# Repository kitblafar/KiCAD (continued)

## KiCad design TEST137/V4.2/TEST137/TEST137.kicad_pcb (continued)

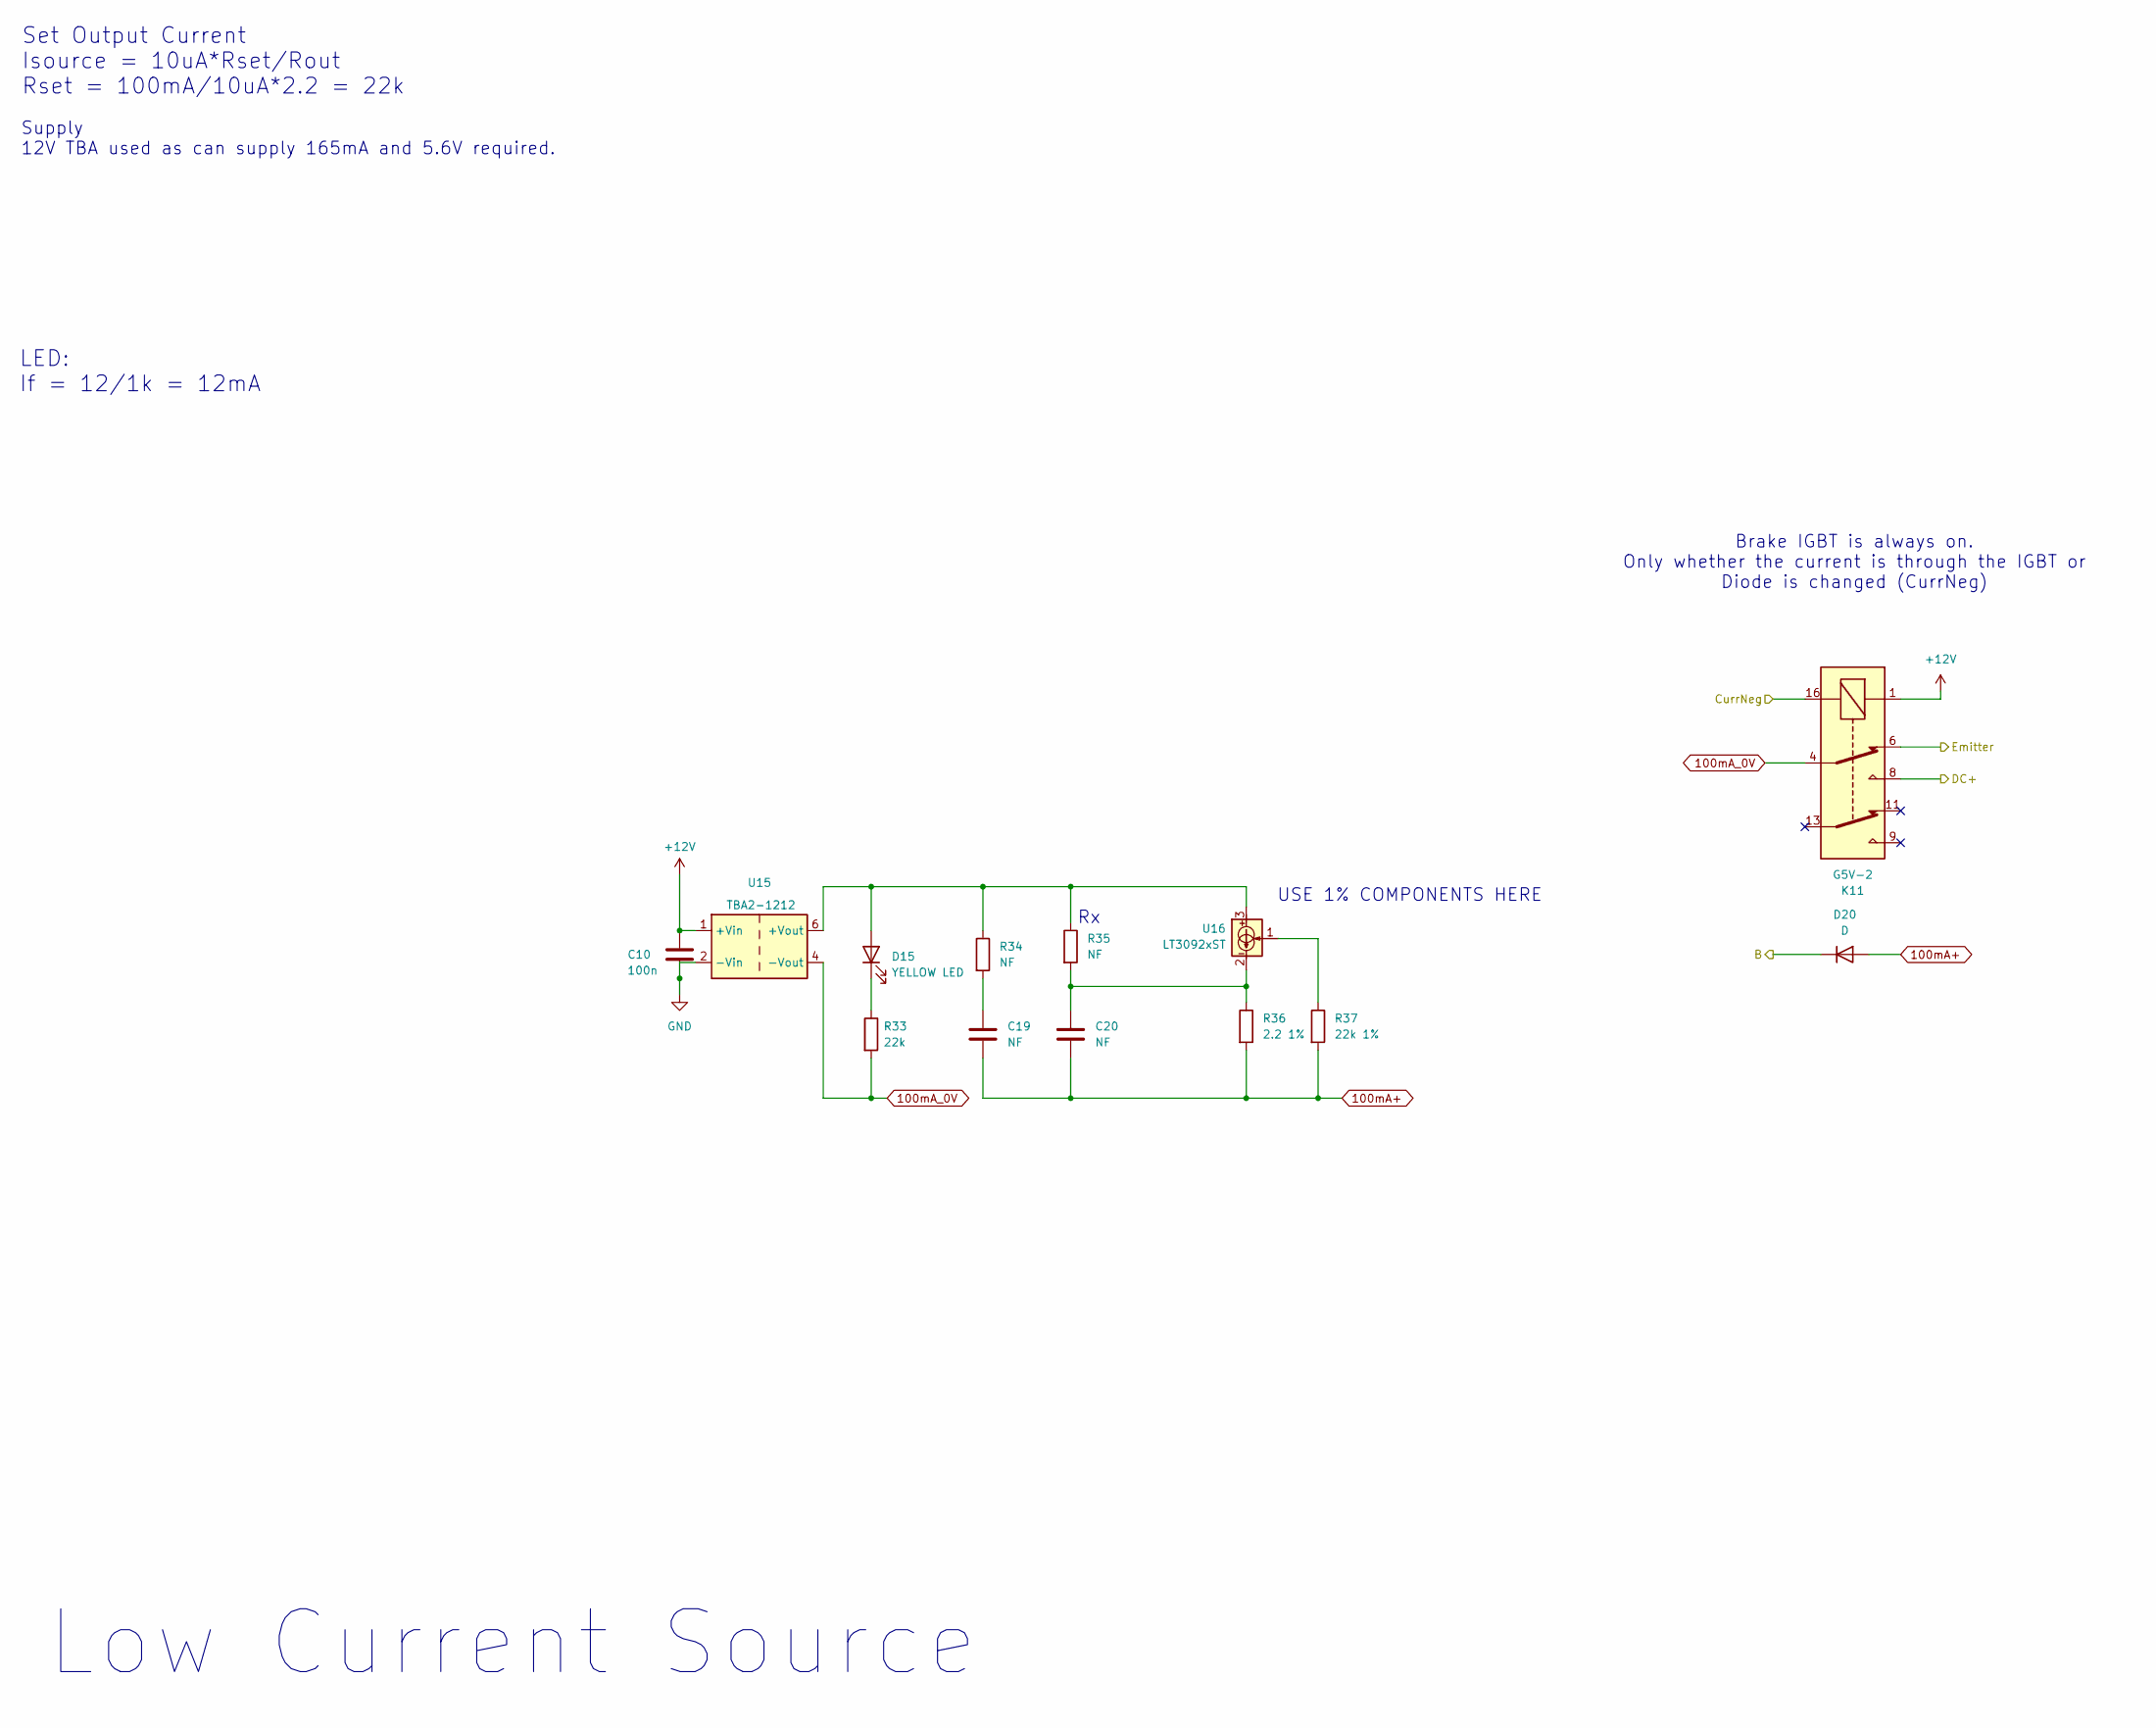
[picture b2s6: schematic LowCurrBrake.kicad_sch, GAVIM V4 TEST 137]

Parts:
C10: 100n; C_0603_1608Metric_Pad1.08x0.95mm_HandSolder
C19, C20: NF; C_0603_1608Metric_Pad1.08x0.95mm_HandSolder
D15: YELLOW LED; LED_D4.0mm
D20: D; BAS16
K11: G5V-2; Relay_DPDT_Omron_G5V-2
R33: 22k; R_0603_1608Metric_Pad0.98x0.95mm_HandSolder
R34, R35: NF; R_0603_1608Metric_Pad0.98x0.95mm_HandSolder
R36: 2.2 1%; R_0603_1608Metric_Pad0.98x0.95mm_HandSolder
R37: 22k 1%; R_0603_1608Metric_Pad0.98x0.95mm_HandSolder
U15: TBA2-1212; TBA21213
U16: LT3092xST; SOT-223-3_TabPin2

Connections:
100mA+: C19.2, C20.2, D20.2 (A), R36.2, R37.2
100mA_0V: K11.4, R33.2, U15.4 (-Vout)
+12V: C10.1, K11.1, U15.1 (+Vin); also elsewhere on the board
/Low Current/CurrNeg12V: K11.16; also elsewhere on the board
B: D20.1 (K); also elsewhere on the board
Bem: K11.6; also elsewhere on the board
DC+: K11.8; also elsewhere on the board
GND: C10.2, U15.2 (-Vin); also elsewhere on the board
unnamed: C19.1, R34.2
unnamed: C20.1, R35.2, R36.1, U16.2
unnamed: D15.2 (A), R34.1, R35.1, U15.6 (+Vout), U16.3
unnamed: D15.1 (K), R33.1
unnamed: R37.1, U16.1

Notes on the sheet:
Supply 12V TBA used as can supply 165mA and 5.6V required.
Brake IGBT is always on. Only whether the current is through the IGBT or Diode is changed (CurrNeg)
LED: If = 12/1k = 12mA
Set Output Current Isource = 10uA*Rset/Rout Rset = 100mA/10uA*2.2 = 22k
USE 1% COMPONENTS HERE
Low Current Source

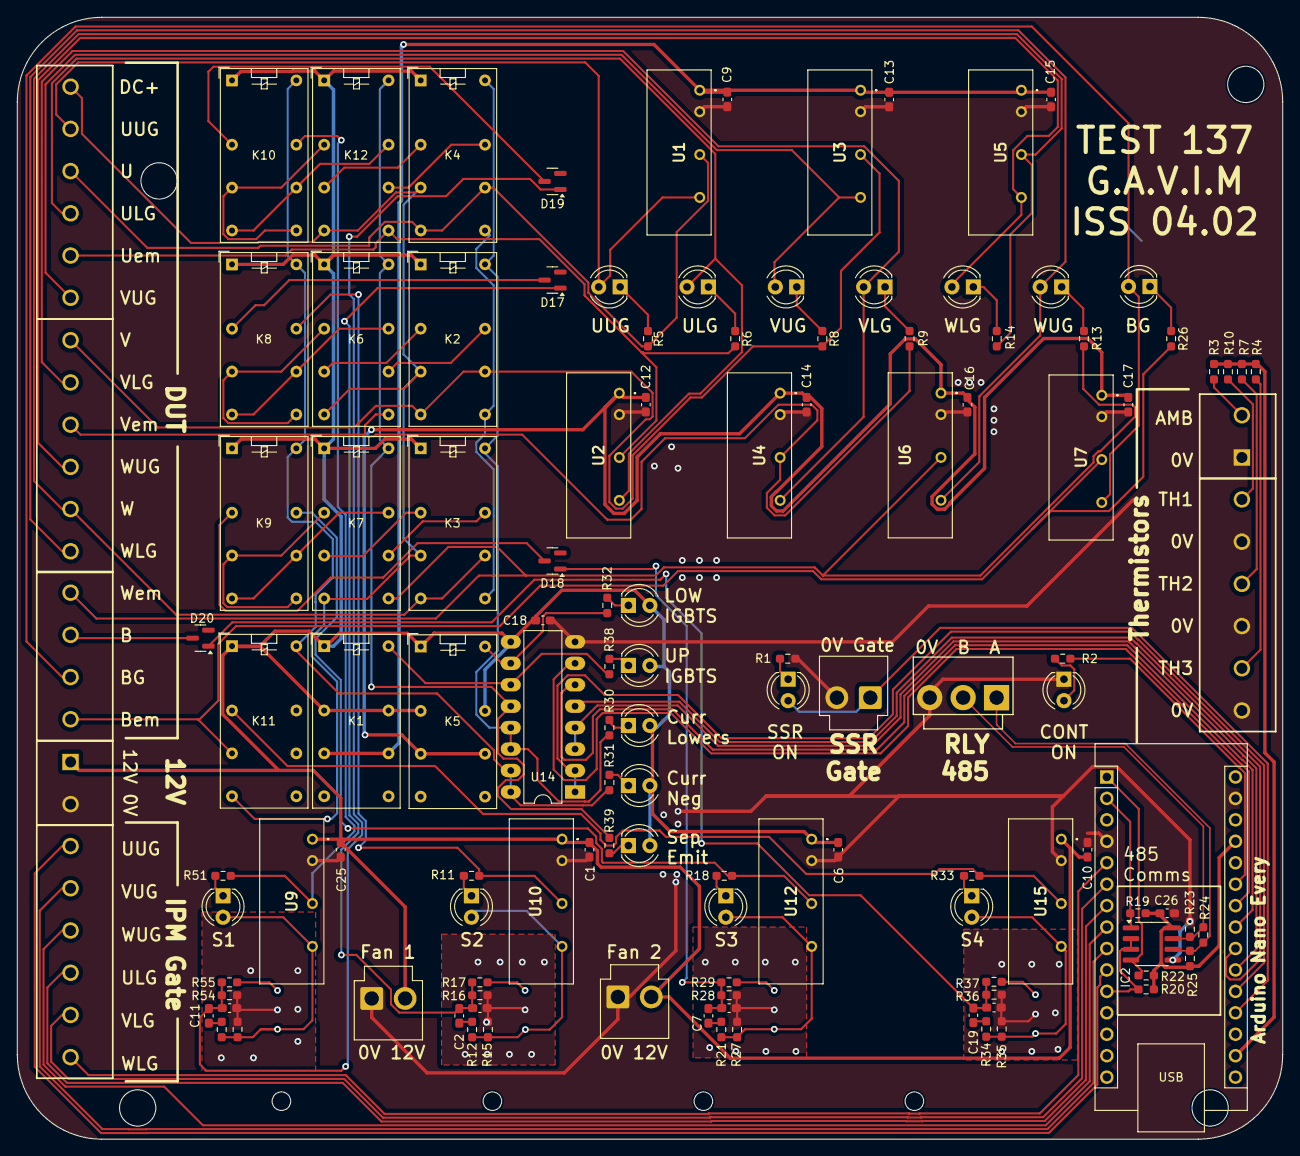
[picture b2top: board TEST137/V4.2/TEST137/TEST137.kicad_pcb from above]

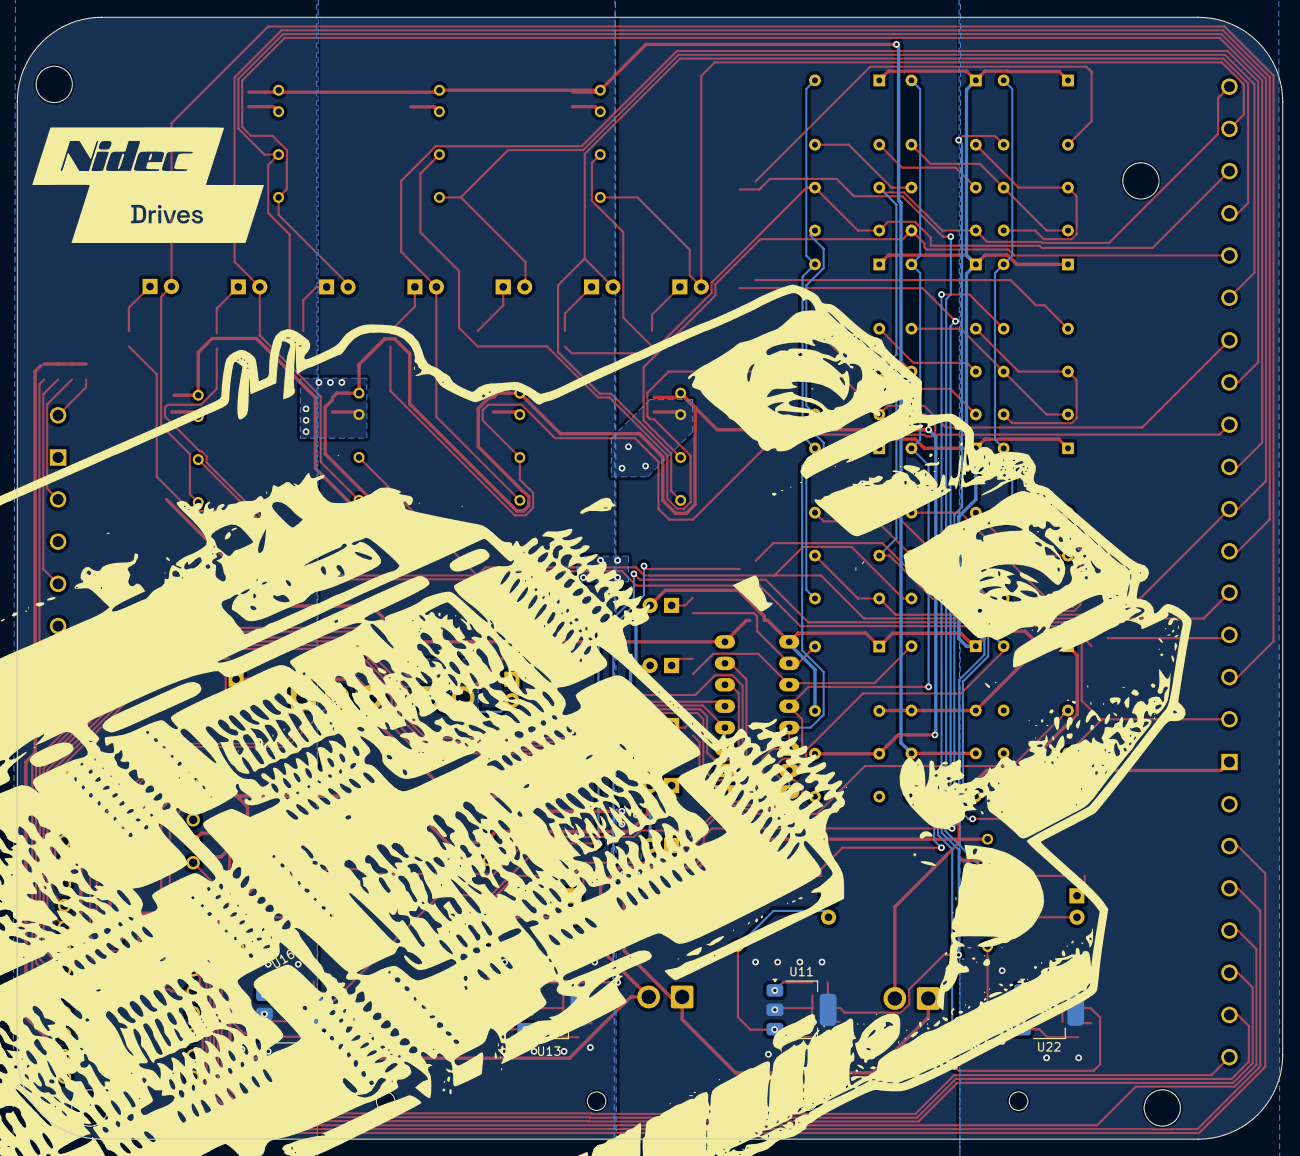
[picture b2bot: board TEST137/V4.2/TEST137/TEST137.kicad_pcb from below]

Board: 2 copper layers, 149.9 x 132.9 mm, 128 parts (4 on the bottom side), 107 nets.

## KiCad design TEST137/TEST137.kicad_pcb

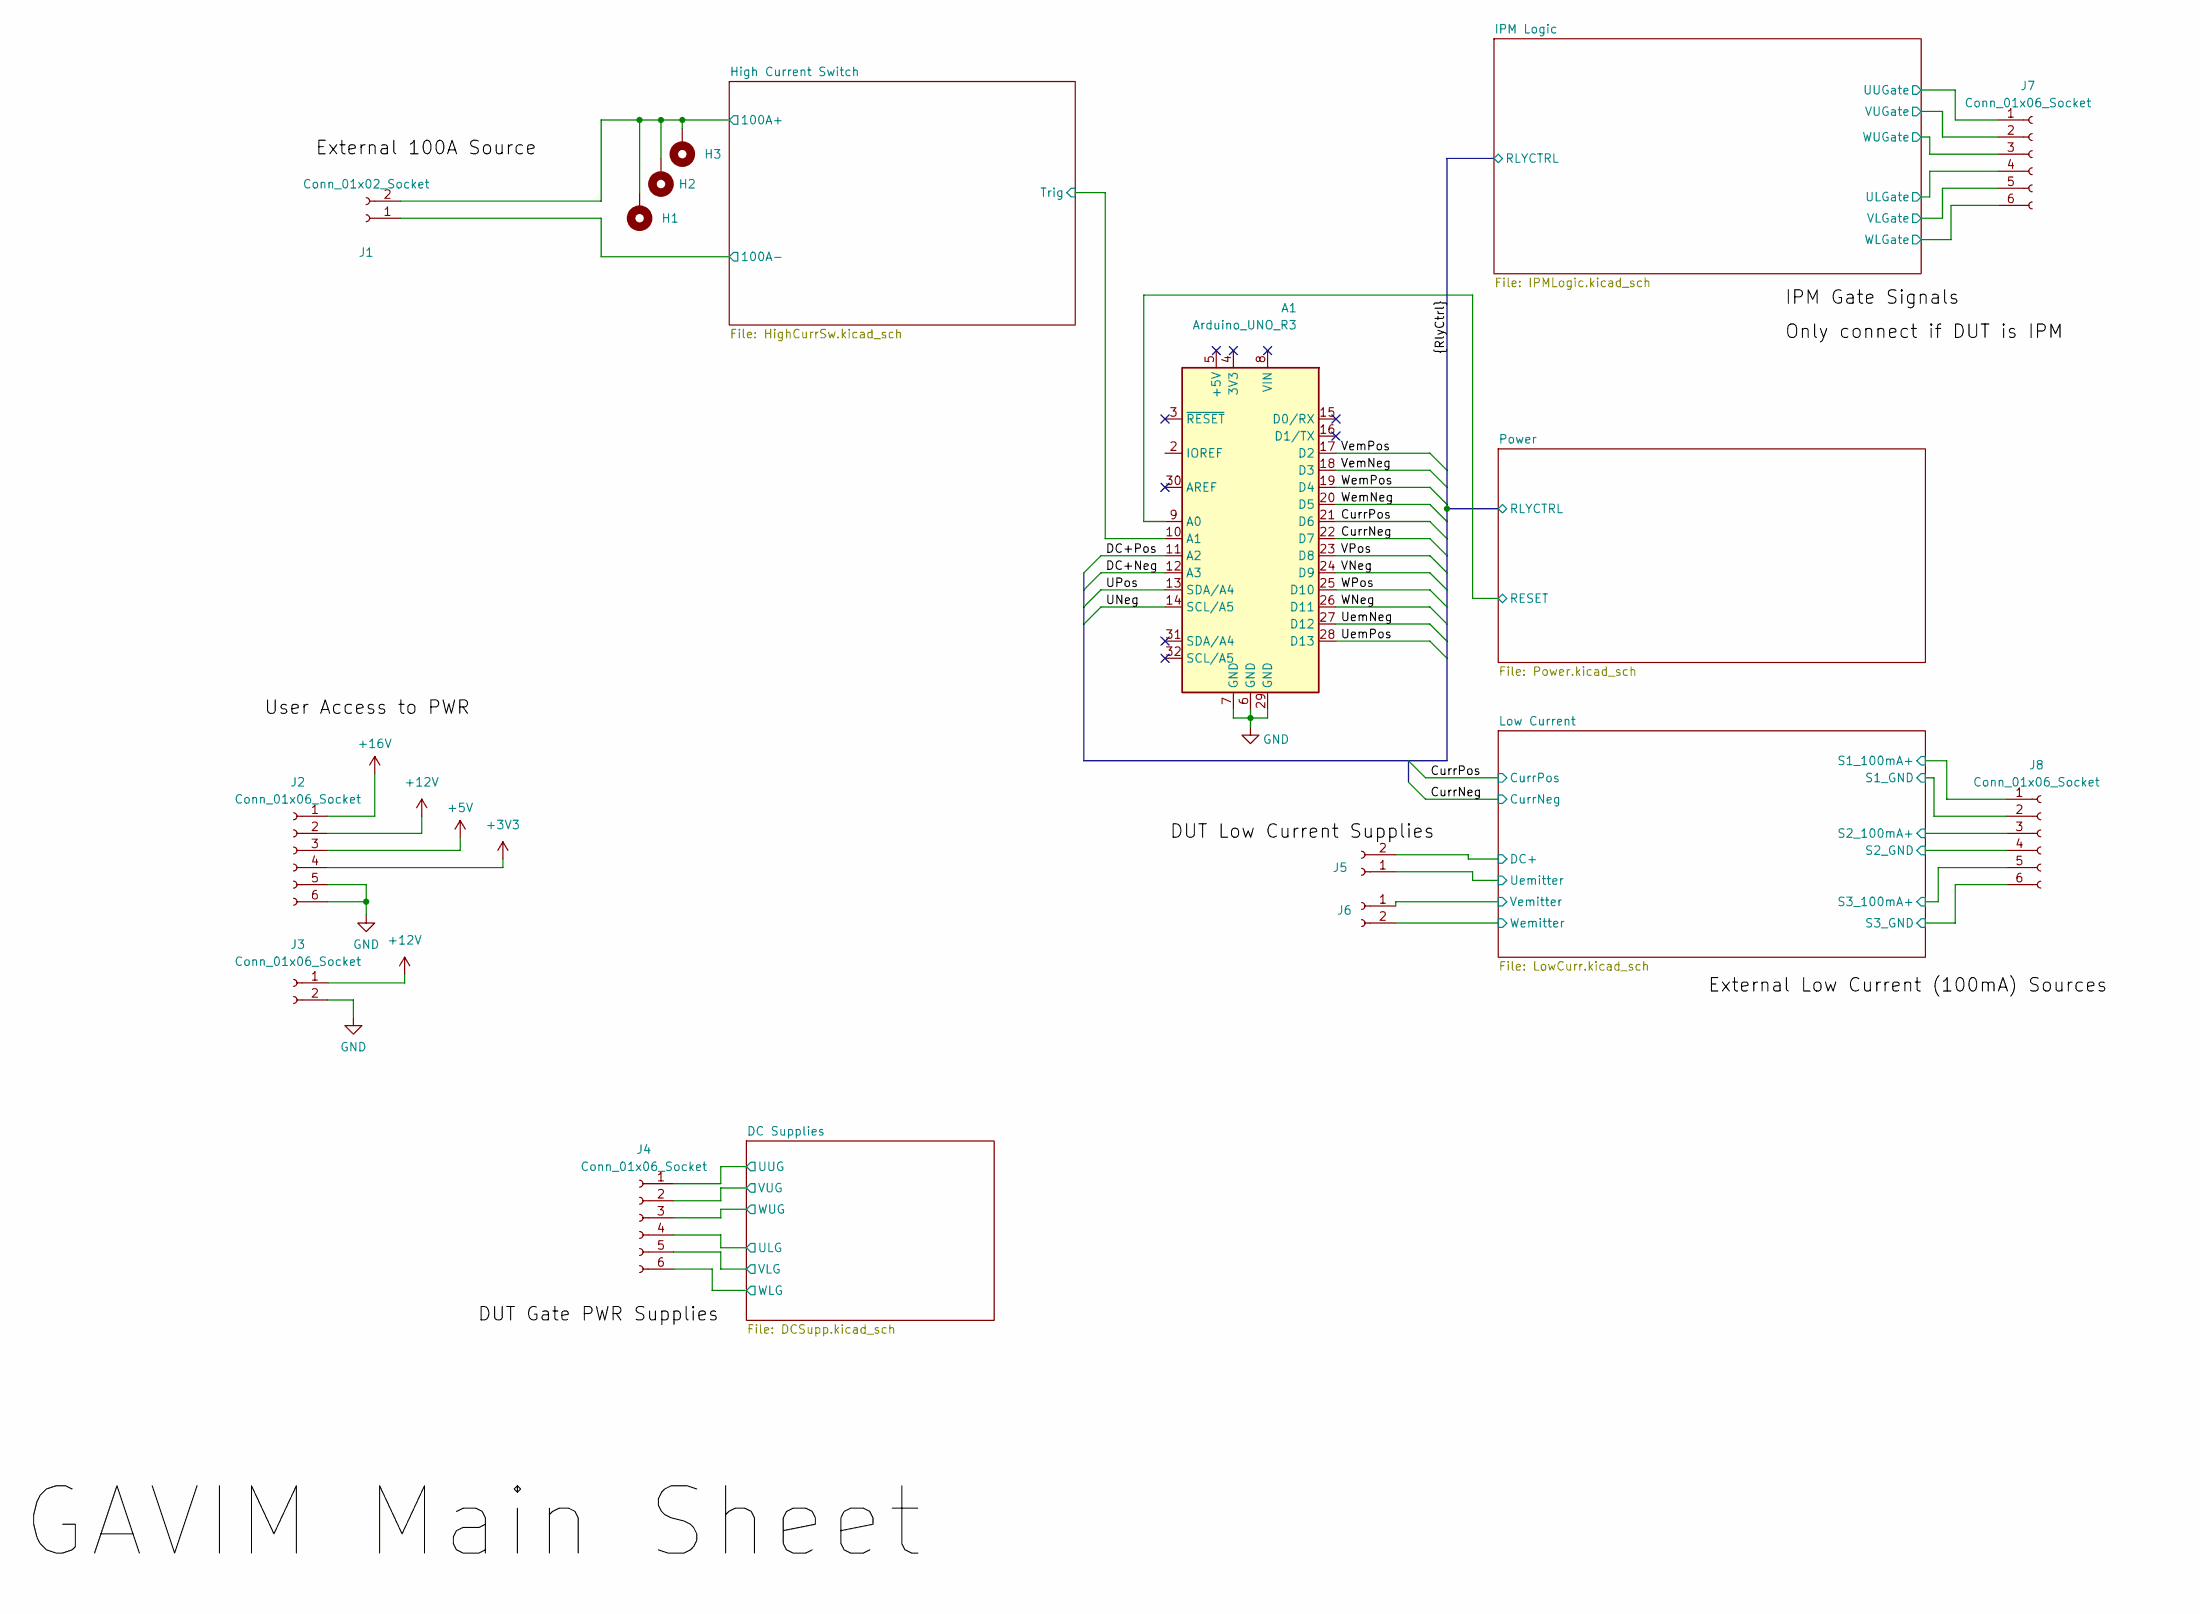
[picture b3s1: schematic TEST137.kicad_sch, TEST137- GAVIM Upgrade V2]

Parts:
A1: Arduino_UNO_R3; Arduino_UNO_R3_WithMountingHoles
H1, H2, H3: MountingHole_Pad_Cust; MountingHole_4.3mm_M4_DIN965_Pad
J1: Conn_01x02_Socket; 1932588
J2, J4, J7, J8: Conn_01x06_Socket; TB00150006BE
J3, J5, J6: Conn_01x06_Socket; TB003-500-P02BE

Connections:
+3V3: J2.4; also elsewhere on the board
+12V: J2.2, J3.1; also elsewhere on the board
+16V: J2.1; also elsewhere on the board
/CurrNeg: A1.22 (D7); also elsewhere on the board
/CurrPos: A1.21 (D6); also elsewhere on the board
/DC Supplies/ULG: J4.4; also elsewhere on the board
/DC Supplies/UUG: J4.1; also elsewhere on the board
/DC Supplies/VLG: J4.5; also elsewhere on the board
/DC Supplies/VUG: J4.2; also elsewhere on the board
/DC Supplies/WLG: J4.6; also elsewhere on the board
/DC Supplies/WUG: J4.3; also elsewhere on the board
/DC+Neg: A1.12 (A3); also elsewhere on the board
/DC+Pos: A1.11 (A2); also elsewhere on the board
/High Current Switch/100A+: H1.1, H2.1, H3.1, J1.2; also elsewhere on the board
/High Current Switch/100A-: J1.1; also elsewhere on the board
/High Current Switch/Trig: A1.10 (A1); also elsewhere on the board
/IPM Logic/ULGate: J7.4; also elsewhere on the board
/IPM Logic/UUGate: J7.1; also elsewhere on the board
/IPM Logic/VLGate: J7.5; also elsewhere on the board
/IPM Logic/VUGate: J7.2; also elsewhere on the board
/IPM Logic/WLGate: J7.6; also elsewhere on the board
/IPM Logic/WUGate: J7.3; also elsewhere on the board
/Low Current/DC+: J5.2; also elsewhere on the board
/Low Current/S1_100mA+: J8.1; also elsewhere on the board
/Low Current/S1_GND: J8.2; also elsewhere on the board
/Low Current/S2_100mA+: J8.3; also elsewhere on the board
/Low Current/S2_GND: J8.4; also elsewhere on the board
/Low Current/S3_100mA+: J8.5; also elsewhere on the board
/Low Current/S3_GND: J8.6; also elsewhere on the board
/Low Current/Uemitter: J5.1; also elsewhere on the board
/Low Current/Vemitter: J6.1; also elsewhere on the board
/Low Current/Wemitter: J6.2; also elsewhere on the board
/UNeg: A1.14 (SCL/A5); also elsewhere on the board
/UPos: A1.13 (SDA/A4); also elsewhere on the board
/UemNeg: A1.27 (D12); also elsewhere on the board
/UemPos: A1.28 (D13); also elsewhere on the board
/VNeg: A1.24 (D9); also elsewhere on the board
/VPos: A1.23 (D8); also elsewhere on the board
/VemNeg: A1.18 (D3); also elsewhere on the board
/VemPos: A1.17 (D2); also elsewhere on the board
/WNeg: A1.26 (D11); also elsewhere on the board
/WPos: A1.25 (D10); also elsewhere on the board
/WemNeg: A1.20 (D5); also elsewhere on the board
/WemPos: A1.19 (D4); also elsewhere on the board
GND: A1.6 (GND), A1.7 (GND), A1.29 (GND), J2.5, J2.6, J3.2; also elsewhere on the board

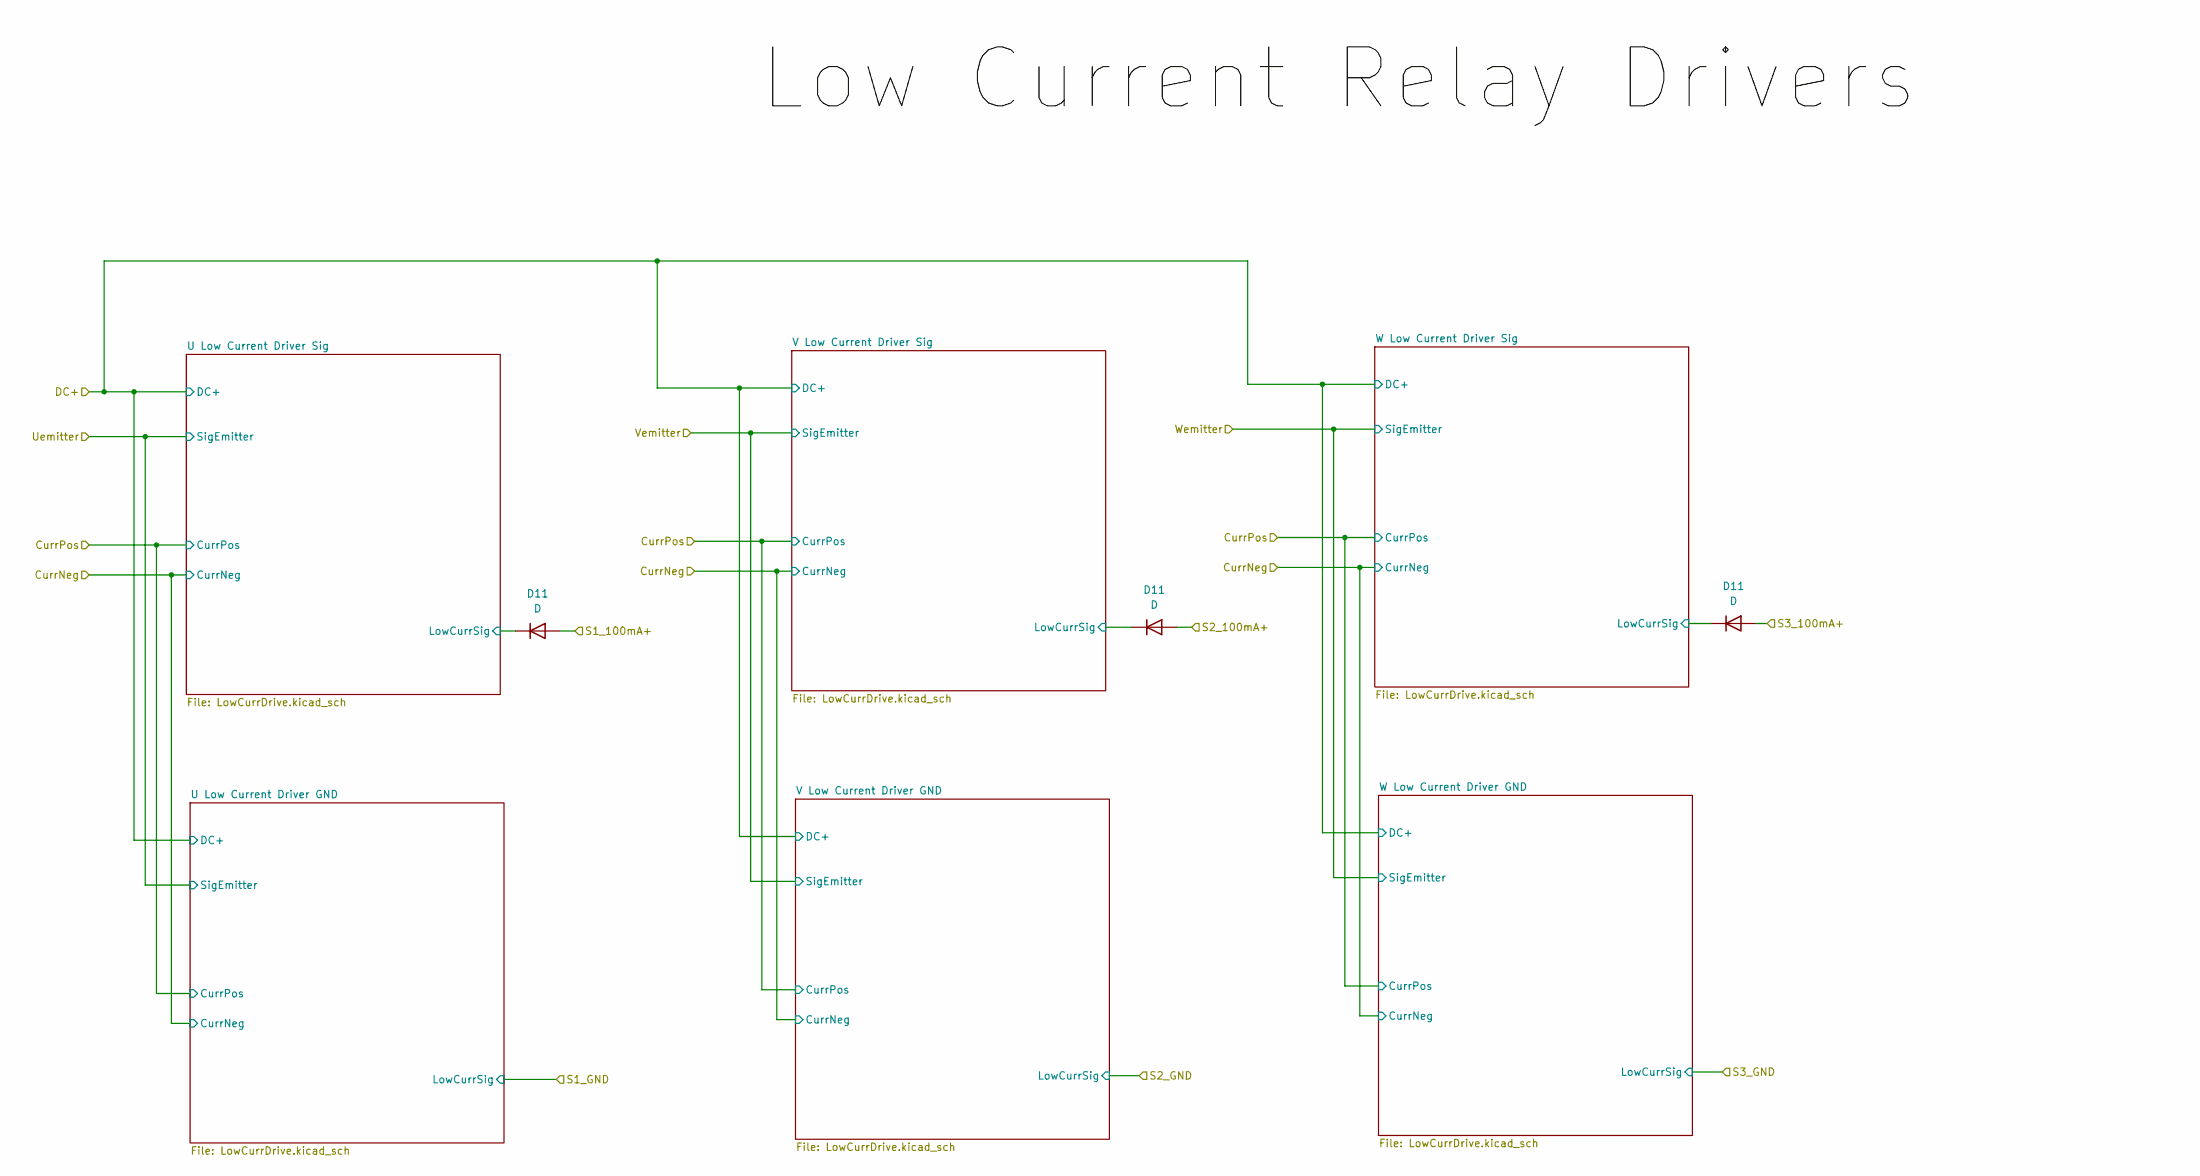
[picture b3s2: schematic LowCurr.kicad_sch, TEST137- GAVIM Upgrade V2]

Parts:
D11: D; D_DO-41_SOD81_P12.70mm_Horizontal

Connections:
+12V: D11.1 (K); also elsewhere on the board
unnamed 61: D11.2 (A); also elsewhere on the board

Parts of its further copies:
D24, D25, D26: D; D_DO-41_SOD81_P12.70mm_Horizontal

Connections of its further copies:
/Low Current/S1_100mA+: D26.2 (A); also elsewhere on the board
/Low Current/S2_100mA+: D24.2 (A); also elsewhere on the board
/Low Current/S3_100mA+: D25.2 (A); also elsewhere on the board
/Low Current/U Low Current Driver Sig/LowCurrSig: D26.1 (K); also elsewhere on the board
/Low Current/V Low Current Driver Sig/LowCurrSig: D24.1 (K); also elsewhere on the board
/Low Current/W Low Current Driver Sig/LowCurrSig: D25.1 (K); also elsewhere on the board

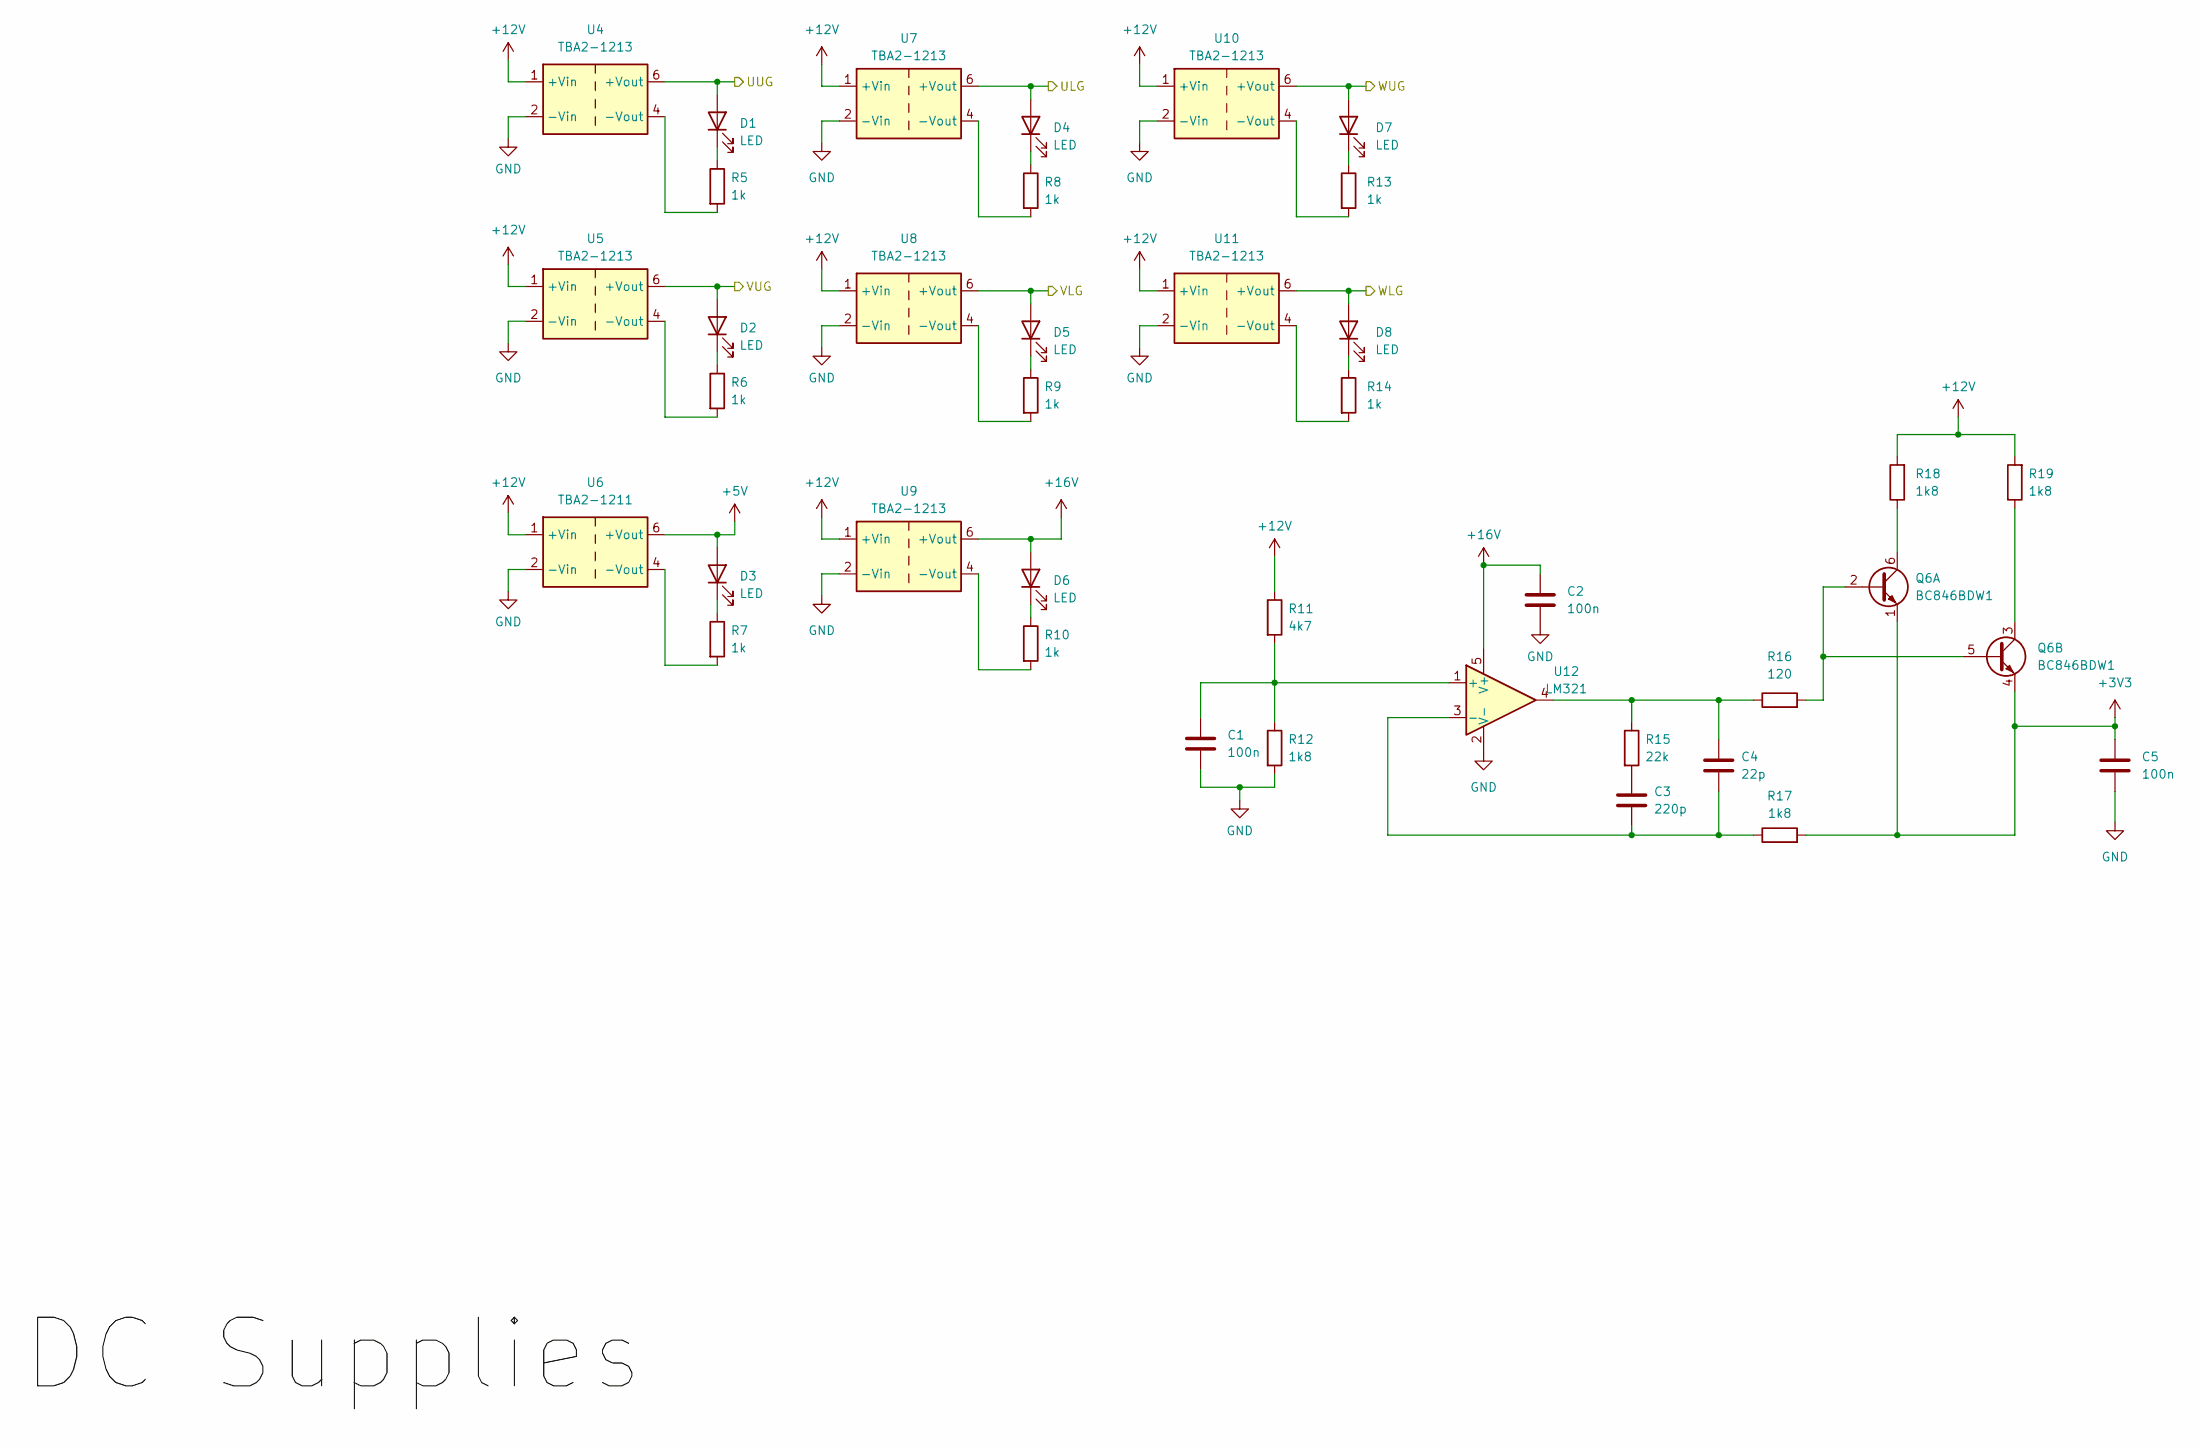
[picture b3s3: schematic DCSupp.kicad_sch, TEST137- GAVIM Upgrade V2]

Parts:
C1, C2, C5: 100n; C_0603_1608Metric_Pad1.08x0.95mm_HandSolder
C3: 220p; C_0603_1608Metric_Pad1.08x0.95mm_HandSolder
C4: 22p; C_0603_1608Metric_Pad1.08x0.95mm_HandSolder
D1, D2, D3, D4, D5, D6, D7, D8: LED; LED_D4.0mm
Q6: BC846BDW1; SOT-363_SC-70-6
R5, R6, R7, R8, R9, R10, R13, R14: 1k; R_0603_1608Metric_Pad0.98x0.95mm_HandSolder
R11: 4k7; R_0603_1608Metric_Pad0.98x0.95mm_HandSolder
R12, R17, R18, R19: 1k8; R_0603_1608Metric_Pad0.98x0.95mm_HandSolder
R15: 22k; R_0603_1608Metric_Pad0.98x0.95mm_HandSolder
R16: 120; R_0603_1608Metric_Pad0.98x0.95mm_HandSolder
U4, U5, U7, U8, U9, U10, U11: TBA2-1213; Converter_DCDC_TRACO_TBA2-xxxx_Single_THT
U6: TBA2-1211; Converter_DCDC_TRACO_TBA2-xxxx_Single_THT
U12: LM321; SOT-23-5; Manufacturer_Part_Number LM321

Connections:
+3V3: C5.1, Q6.1 (E1), Q6.4 (E2), R17.2; also elsewhere on the board
+12V: R11.1, R18.2, R19.2, U4.1 (+Vin), U5.1 (+Vin), U6.1 (+Vin), U7.1 (+Vin), U8.1 (+Vin), U9.1 (+Vin), U10.1 (+Vin), U11.1 (+Vin); also elsewhere on the board
+16V: C2.1, D6.2 (A), U9.6 (+Vout), U12.5 (V+); also elsewhere on the board
/DC Supplies/ULG: D4.2 (A), U7.6 (+Vout); also elsewhere on the board
/DC Supplies/UUG: D1.2 (A), U4.6 (+Vout); also elsewhere on the board
/DC Supplies/VLG: D5.2 (A), U8.6 (+Vout); also elsewhere on the board
/DC Supplies/VUG: D2.2 (A), U5.6 (+Vout); also elsewhere on the board
/DC Supplies/WLG: D8.2 (A), U11.6 (+Vout); also elsewhere on the board
/DC Supplies/WUG: D7.2 (A), U10.6 (+Vout); also elsewhere on the board
GND: C1.2, C2.2, C5.2, R12.2, U4.2 (-Vin), U5.2 (-Vin), U6.2 (-Vin), U7.2 (-Vin), U8.2 (-Vin), U9.2 (-Vin), U10.2 (-Vin), U11.2 (-Vin), U12.2 (V-); also elsewhere on the board
unnamed: C3.1, R15.2
unnamed: C4.1, R15.1, R16.1, U12.4
unnamed: D1.1 (K), R5.1
unnamed: D2.1 (K), R6.1
unnamed: D3.1 (K), R7.1
unnamed: D4.1 (K), R8.1
unnamed: D5.1 (K), R9.1
unnamed: D6.1 (K), R10.1
unnamed: D7.1 (K), R13.1
unnamed: D8.1 (K), R14.1
unnamed: Q6.2 (B1), Q6.5 (B2), R16.2
unnamed: Q6.6 (C1), R18.1
unnamed: Q6.3 (C2), R19.1
unnamed: R5.2, U4.4 (-Vout)
unnamed: R6.2, U5.4 (-Vout)
unnamed: R7.2, U6.4 (-Vout)
unnamed: R8.2, U7.4 (-Vout)
unnamed: R9.2, U8.4 (-Vout)
unnamed: R10.2, U9.4 (-Vout)
unnamed: R13.2, U10.4 (-Vout)
unnamed: R14.2, U11.4 (-Vout)
unnamed: C1.1, R11.2, R12.1, U12.1 (+)
unnamed: C3.2, C4.2, R17.1, U12.3 (-)
